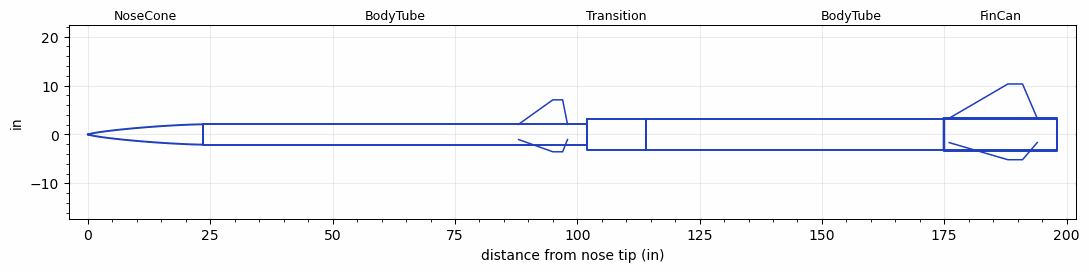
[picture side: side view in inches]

<RASAeroDocument>
 <FileVersion>2</FileVersion>
 <RocketDesign>
  <NoseCone>
   <Length>23.5</Length>
   <Diameter>4.1534</Diameter>
   <Shape>Von Karman Ogive</Shape>
   <Location>0</Location>
  </NoseCone>
  <BodyTube>
   <Length>78.5</Length>
   <Diameter>4.1534</Diameter>
   <Location>23.5</Location>
   <Fin>
    <Count>3</Count>
    <Chord>10</Chord>
    <Span>5</Span>
    <SweepDistance>7</SweepDistance>
    <TipChord>2</TipChord>
    <Thickness>0.125</Thickness>
    <Location>14</Location>
    <AirfoilSection>Square</AirfoilSection>
   </Fin>
  </BodyTube>
  <Transition>
   <Length>12</Length>
   <Diameter>6.51</Diameter>
   <Location>102</Location>
   <RearDiameter>6.51</RearDiameter>
  </Transition>
  <BodyTube>
   <Length>84</Length>
   <Diameter>6.51</Diameter>
   <Location>114</Location>
  </BodyTube>
  <FinCan>
   <Length>23</Length>
   <Diameter>6.635</Diameter>
   <InsideDiameter>6.51</InsideDiameter>
   <Location>198</Location>
   <ShoulderLength>0.125</ShoulderLength>
   <Offset>-23</Offset>
   <Fin>
    <Count>3</Count>
    <Chord>18</Chord>
    <Span>7</Span>
    <SweepDistance>12</SweepDistance>
    <TipChord>3</TipChord>
    <Thickness>0.125</Thickness>
    <Location>22</Location>
    <AirfoilSection>Square</AirfoilSection>
   </Fin>
  </FinCan>
  <Surface>Smooth (Zero Roughness)</Surface>
  <ModifiedBarrowman>False</ModifiedBarrowman>
  <Turbulence>False</Turbulence>
  <UseBooster1>False</UseBooster1>
  <UseBooster2>False</UseBooster2>
 </RocketDesign>
 <LaunchSite>
  <Altitude>3000</Altitude>
  <Pressure>30.3</Pressure>
  <RodAngle>1</RodAngle>
  <RodLength>25</RodLength>
  <Temperature>90</Temperature>
  <WindSpeed>12</WindSpeed>
 </LaunchSite>
 <Recovery>
  <Altitude1>1000</Altitude1>
  <Altitude2>1000</Altitude2>
  <DeviceType1>None</DeviceType1>
  <DeviceType2>None</DeviceType2>
  <Event1>False</Event1>
  <Event2>False</Event2>
  <Size1>1</Size1>
  <Size2>1</Size2>
  <EventType1>None</EventType1>
  <EventType2>None</EventType2>
  <CD1>1.33</CD1>
  <CD2>1.33</CD2>
 </Recovery>
</RASAeroDocument>
